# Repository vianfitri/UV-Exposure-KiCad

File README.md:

# UV-Exposure-KiCad

Create PCB Layout using KiCad-Layout for LED based UV Exposure Lighting

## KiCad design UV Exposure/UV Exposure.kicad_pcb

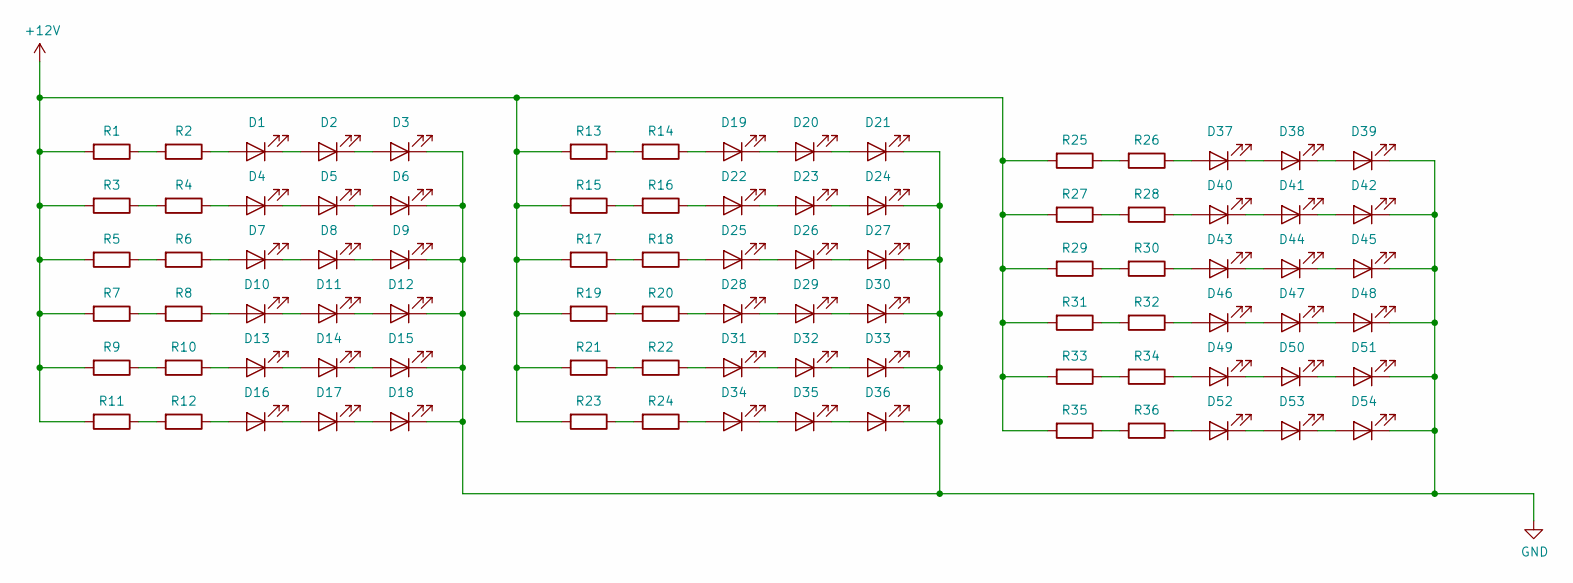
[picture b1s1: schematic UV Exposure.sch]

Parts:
D1, D2, D3, D4, D5, D6, D7, D8, D9, D10, D11, D12, D13, D14, D15, D16, D17, D18, D19, D20, D21, D22, D23, D24, D25, D26, D27, D28, D29, D30, D31, D32, D33, D34, D35, D36, D37, D38, D39, D40, D41, D42, D43, D44, D45, D46, D47, D48, D49, D50, D51, D52, D53, D54: LED
R1, R2, R3, R4, R5, R6, R7, R8, R9, R10, R11, R12, R13, R14, R15, R16, R17, R18, R19, R20, R21, R22, R23, R24, R25, R26, R27, R28, R29, R30, R31, R32, R33, R34, R35, R36: R

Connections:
+12V: R1.2, R3.2, R5.2, R7.2, R9.2, R11.2, R13.2, R15.2, R17.2, R19.2, R21.2, R23.2, R25.2, R27.2, R29.2, R31.2, R33.2, R35.2; also elsewhere on the board
GND: D3.1 (K), D6.1 (K), D9.1 (K), D12.1 (K), D15.1 (K), D18.1 (K), D21.1 (K), D24.1 (K), D27.1 (K), D30.1 (K), D33.1 (K), D36.1 (K), D39.1 (K), D42.1 (K), D45.1 (K), D48.1 (K), D51.1 (K), D54.1 (K); also elsewhere on the board
unnamed: D1.1 (K), D2.2 (A)
unnamed: D1.2 (A), R2.1
unnamed: D2.1 (K), D3.2 (A)
unnamed: D4.1 (K), D5.2 (A)
unnamed: D4.2 (A), R4.1
unnamed: D5.1 (K), D6.2 (A)
unnamed: D7.1 (K), D8.2 (A)
unnamed: D7.2 (A), R6.1
unnamed: D8.1 (K), D9.2 (A)
unnamed: D10.1 (K), D11.2 (A)
unnamed: D10.2 (A), R8.1
unnamed: D11.1 (K), D12.2 (A)
unnamed: D13.1 (K), D14.2 (A)
unnamed: D13.2 (A), R10.1
unnamed: D14.1 (K), D15.2 (A)
unnamed: D16.1 (K), D17.2 (A)
unnamed: D16.2 (A), R12.1
unnamed: D17.1 (K), D18.2 (A)
unnamed: D19.1 (K), D20.2 (A)
unnamed: D19.2 (A), R14.1
unnamed: D20.1 (K), D21.2 (A)
unnamed: D22.1 (K), D23.2 (A)
unnamed: D22.2 (A), R16.1
unnamed: D23.1 (K), D24.2 (A)
unnamed: D25.1 (K), D26.2 (A)
unnamed: D25.2 (A), R18.1
unnamed: D26.1 (K), D27.2 (A)
unnamed: D28.1 (K), D29.2 (A)
unnamed: D28.2 (A), R20.1
unnamed: D29.1 (K), D30.2 (A)
unnamed: D31.1 (K), D32.2 (A)
unnamed: D31.2 (A), R22.1
unnamed: D32.1 (K), D33.2 (A)
unnamed: D34.1 (K), D35.2 (A)
unnamed: D34.2 (A), R24.1
unnamed: D35.1 (K), D36.2 (A)
unnamed: D37.1 (K), D38.2 (A)
unnamed: D37.2 (A), R26.1
unnamed: D38.1 (K), D39.2 (A)
unnamed: D40.1 (K), D41.2 (A)
unnamed: D40.2 (A), R28.1
unnamed: D41.1 (K), D42.2 (A)
unnamed: D43.1 (K), D44.2 (A)
unnamed: D43.2 (A), R30.1
unnamed: D44.1 (K), D45.2 (A)
unnamed: D46.1 (K), D47.2 (A)
unnamed: D46.2 (A), R32.1
unnamed: D47.1 (K), D48.2 (A)
unnamed: D49.1 (K), D50.2 (A)
unnamed: D49.2 (A), R34.1
unnamed: D50.1 (K), D51.2 (A)
unnamed: D52.1 (K), D53.2 (A)
unnamed: D52.2 (A), R36.1
unnamed: D53.1 (K), D54.2 (A)
unnamed: R1.1, R2.2
unnamed: R3.1, R4.2
unnamed: R5.1, R6.2
unnamed: R7.1, R8.2
unnamed: R9.1, R10.2
unnamed: R11.1, R12.2
unnamed: R13.1, R14.2
unnamed: R15.1, R16.2
unnamed: R17.1, R18.2
unnamed: R19.1, R20.2
unnamed: R21.1, R22.2
unnamed: R23.1, R24.2
unnamed: R25.1, R26.2
unnamed: R27.1, R28.2
unnamed: R29.1, R30.2
unnamed: R31.1, R32.2
unnamed: R33.1, R34.2
unnamed: R35.1, R36.2

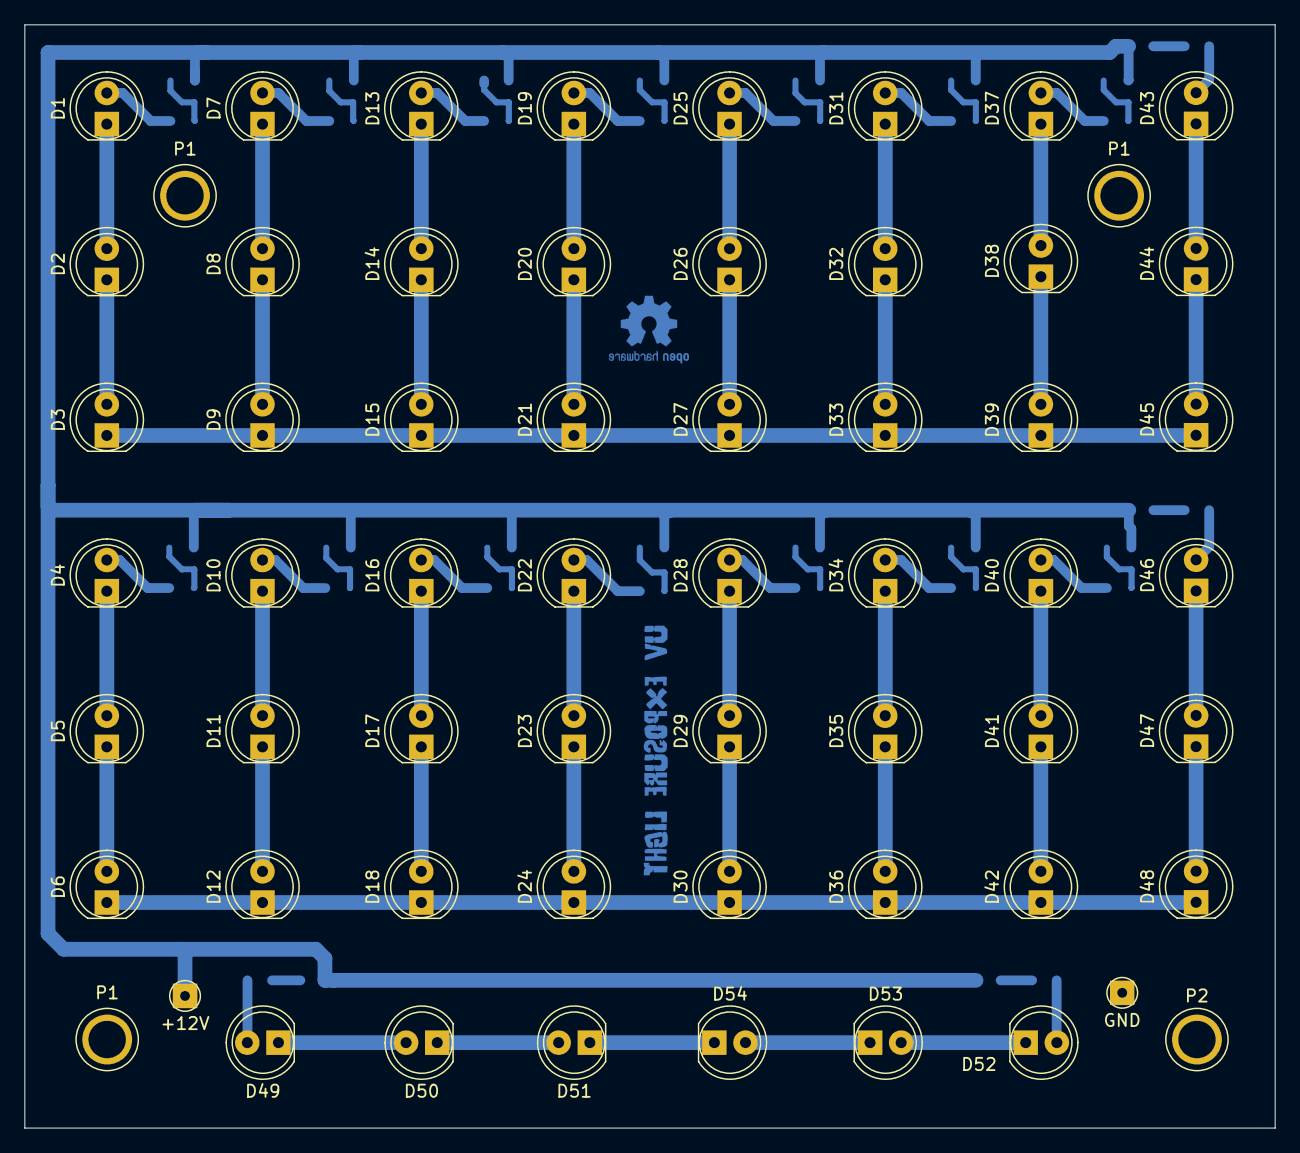
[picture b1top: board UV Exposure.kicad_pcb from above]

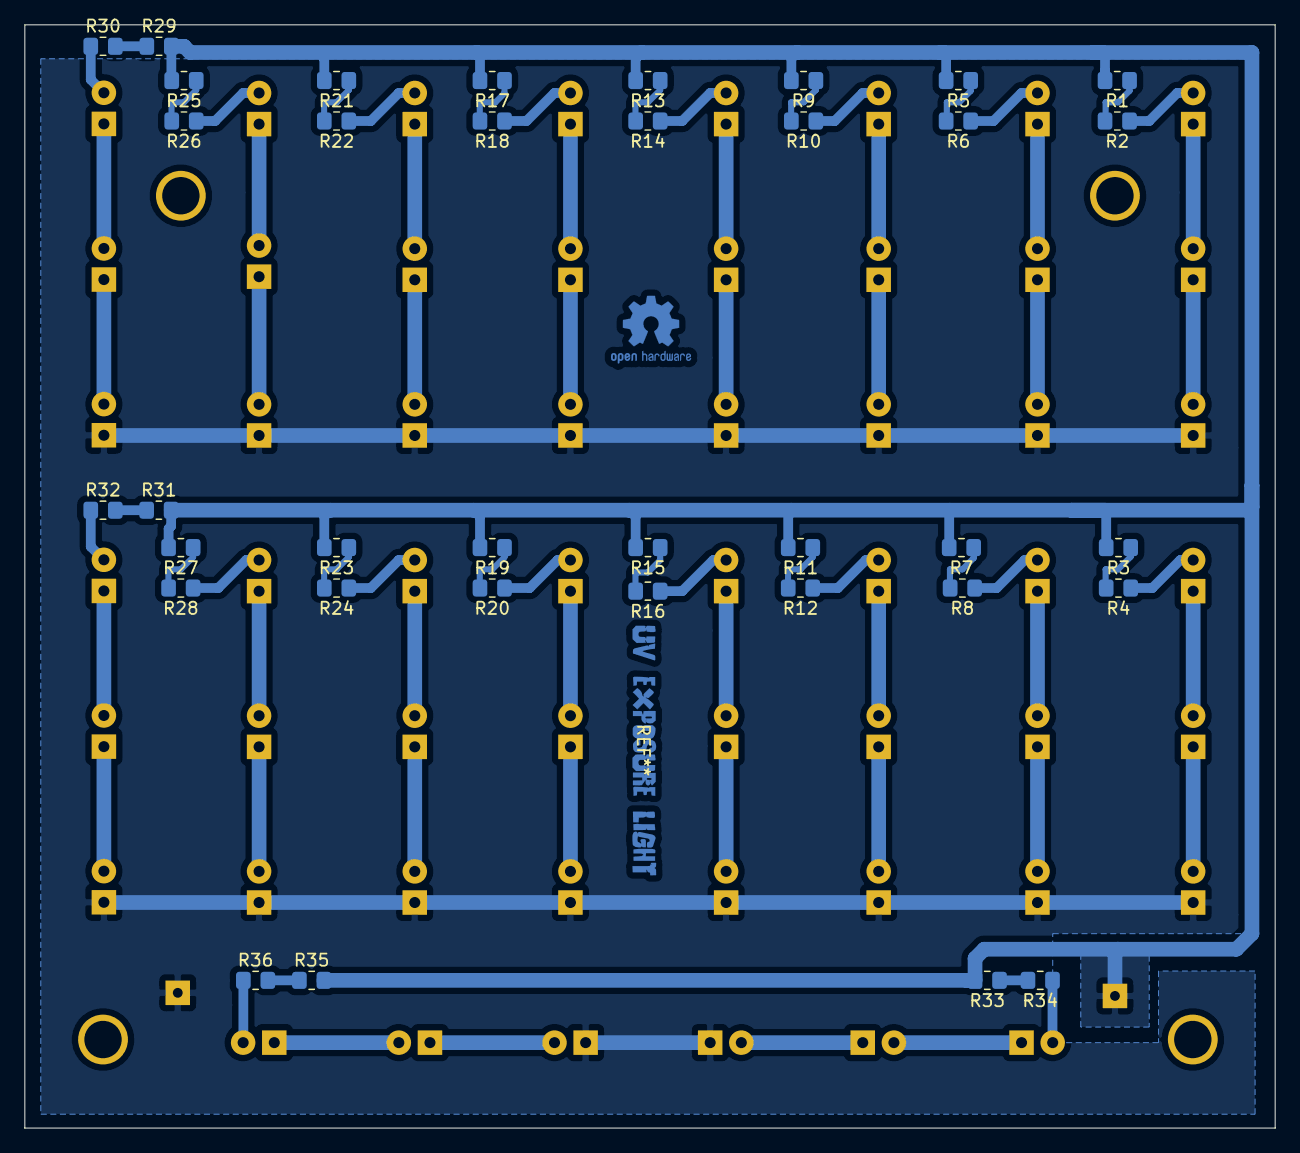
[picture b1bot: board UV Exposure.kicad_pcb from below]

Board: 2 copper layers, 102.0 x 90.0 mm, 96 parts (36 on the bottom side), 74 nets.

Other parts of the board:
+12V: POWER; Pin_D1.0mm_L10.0mm
GND: GROUND; Pin_D1.0mm_L10.0mm
P1, P1#2, P1#3, P2: Conn_01x01; Pin_D1.0mm_L10.0mm

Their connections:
+12V: +12V.1; also elsewhere on the board
GND: GND.1; also elsewhere on the board

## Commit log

2021-02-14 First Commit File project
2021-02-14 Draw schematics
2021-02-14 Assign Footprints and generate netlist
2021-02-14 Create PCB layout
2021-02-15 PCB rearrange
2021-02-15 Reposition SMD Resistor
2021-02-15 Rearrange components
2021-02-15 drawing pcb track
2021-02-16 footprint cache
2021-02-16 Add spacer drill hole
2021-02-16 Update PCB track
2021-02-16 add text for logo
2021-02-17 modify logo cancel
2021-02-17 add logo and rearange track
2021-02-17 cache
